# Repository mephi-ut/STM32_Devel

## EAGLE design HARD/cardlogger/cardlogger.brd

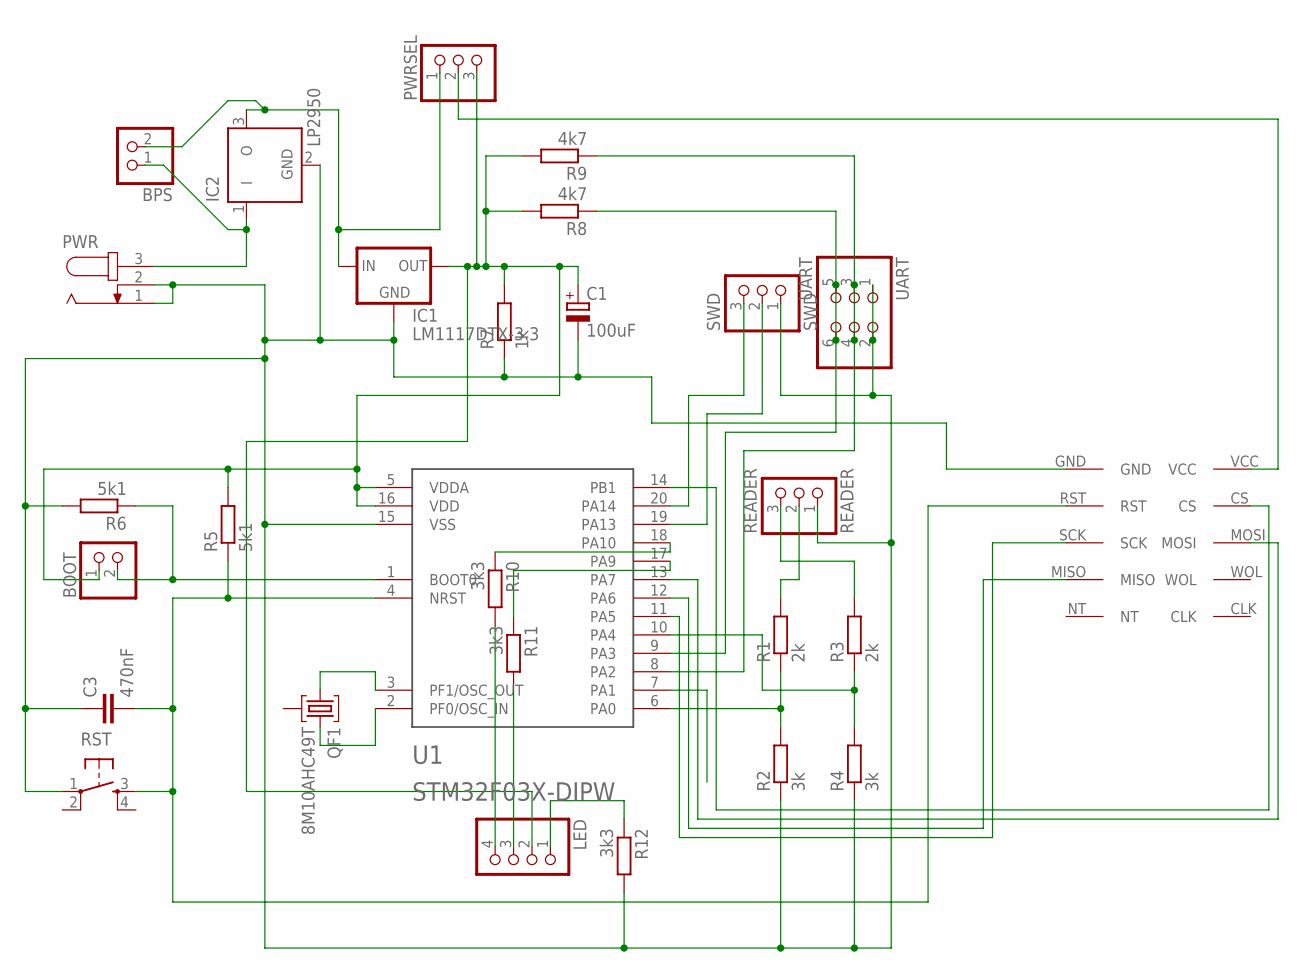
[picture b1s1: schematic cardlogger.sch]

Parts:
BOOT: PINHD-1X2; 1X02
BPS: PINHD-1X2; 1X02
C1: 100uF; SMC_D
C3: 470nF; C0805
IC1: LM1117DTX-3.3; TO252
IC2: LP2950; DPACK
LED: PINHD-1X4; 1X04
PWR: JACK-PLUG0; SPC4077
PWRSEL: PINHD-1X3; 1X03
QF1: 8M10AHC49T; HC49U
R1, R3: 2k; R1206
R2, R4: 3k; R1206
R5, R6: 5k1; R1206
R7: 1k; R1206
R8, R9: 4k7; R1206
R10, R11, R12: 3k3; R1206
READER: READER; 1X03
RST: TAC_SWITCHPTH; TACTILE-PTH
SWD: SWD; 1X03
U1: STM32F03X-DIPW; DIP20W
U$1: ENC28J60
UART: UART; 2X03

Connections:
+3V3: BOOT.1, C1.+, IC1.TAB (OUT), LED.2, PWRSEL.3, R5.2, R7.2, R8.2, R9.2, U1.5 (VDDA), U1.16 (VDD)
BOOT: BOOT.2, R6.1, U1.1 (BOOT0)
CR_0: R1.2, READER.2
CR_1: R3.2, READER.3
EXTI_1: R3.1, R4.2, U1.10 (PA4)
EXYI_0: R1.1, R2.2, U1.6 (PA0)
GND: C1.-, C3.1, IC1.1 (GND), IC2.2 (GND), PWR.1, PWR.2, R2.1, R4.1, R6.2, R7.1, R12.2, READER.1, RST.1, SWD.1, U1.15 (VSS), U$1.GND, UART.1, UART.2
unnamed: SWD.2, U1.19 (PA13)
unnamed: SWD.3, U1.20 (PA14)
unnamed: LED.4, R10.2
unnamed: U1.11 (PA5), U$1.SCK
unnamed: U1.12 (PA6), U$1.MISO
unnamed: U1.13 (PA7), U$1.MOSI
unnamed: U1.14 (PB1), U$1.CS
unnamed: R11.1, U1.17 (PA9)
unnamed: PWRSEL.2, U$1.VCC
unnamed: BPS.1, IC2.1 (I), PWR.3
unnamed: BPS.2, IC1.2 (IN), IC2.3 (O), PWRSEL.1
unnamed: R10.1, U1.18 (PA10)
unnamed: QF1.1, U1.3 (PF1/OSC_OUT)
unnamed: QF1.3, U1.2 (PF0/OSC_IN)
unnamed: LED.3, R11.2
unnamed: LED.1, R12.1
RST: C3.2, R5.1, RST.3, U1.4 (NRST), U$1.RST
RX: R8.1, U1.9 (PA3), UART.5, UART.6
TX: R9.1, U1.8 (PA2), UART.3, UART.4

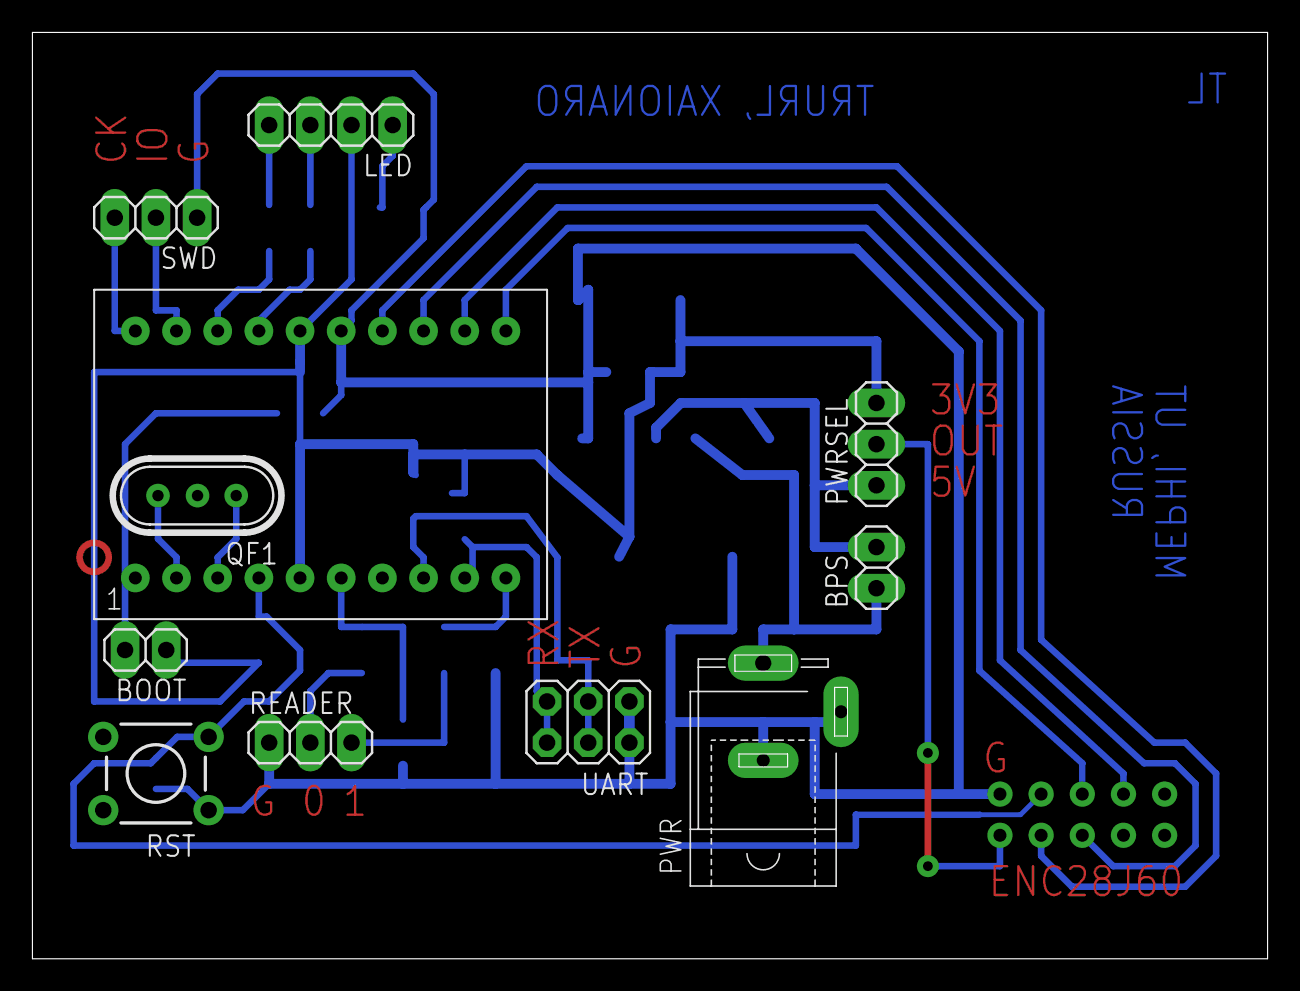
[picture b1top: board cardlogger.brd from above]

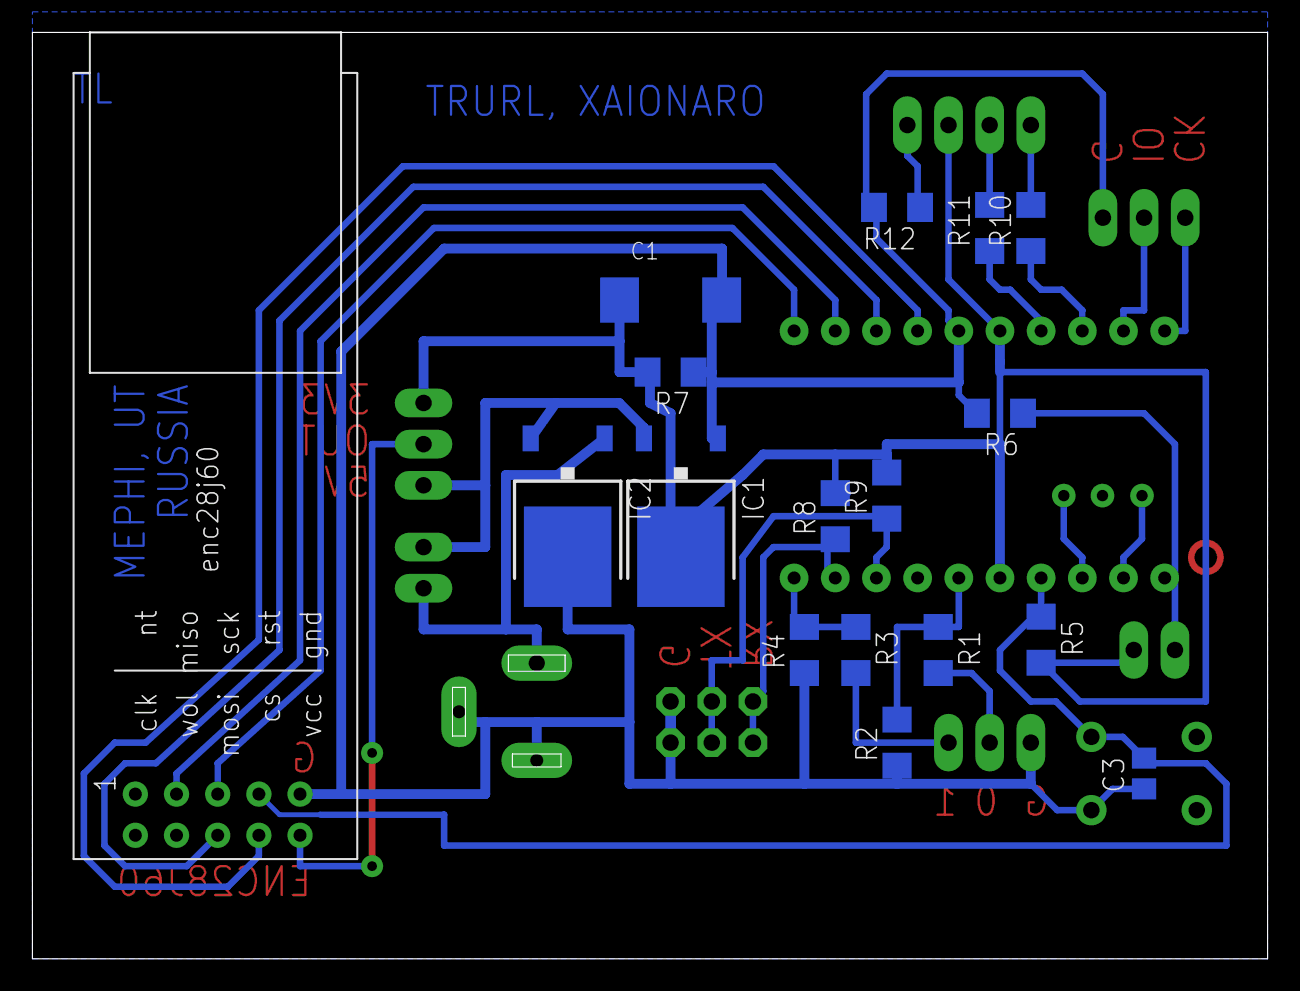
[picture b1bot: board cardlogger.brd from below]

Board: 2 copper layers, 76.2 x 57.1 mm, 28 parts (17 on the bottom side), 26 nets.

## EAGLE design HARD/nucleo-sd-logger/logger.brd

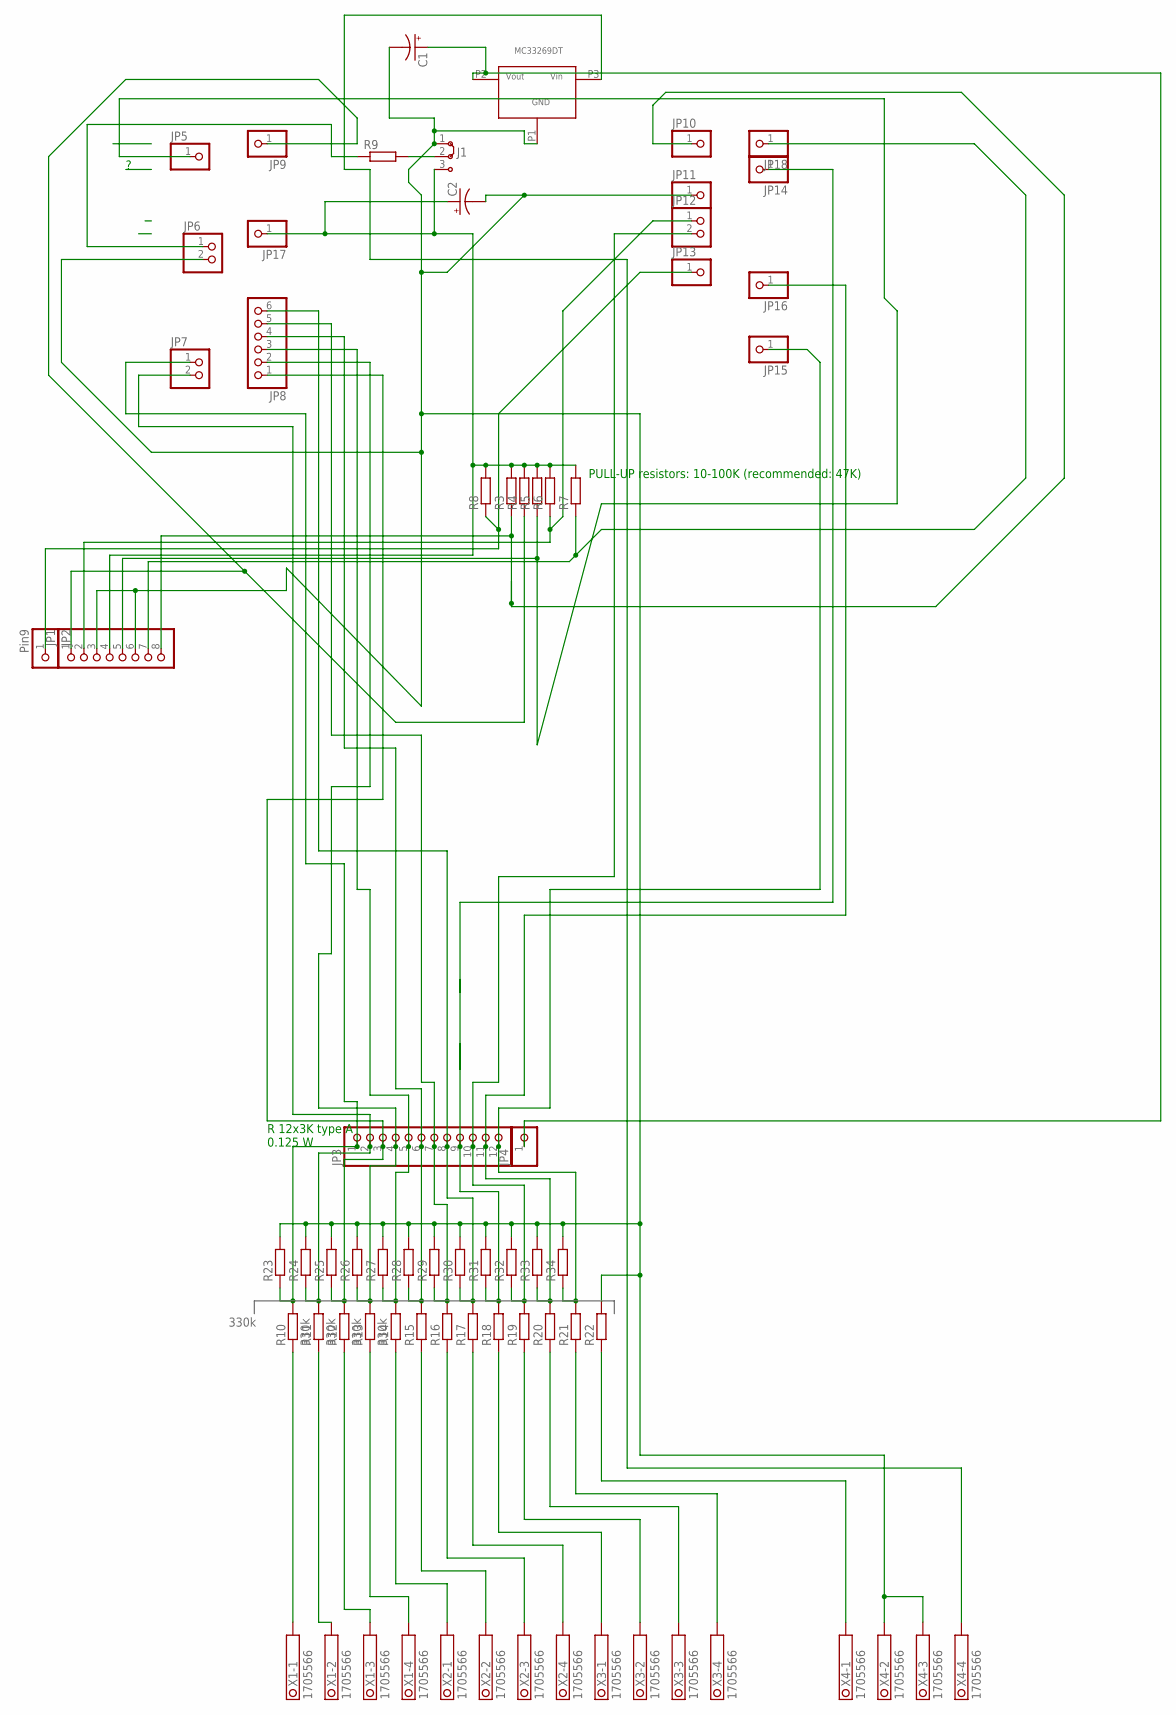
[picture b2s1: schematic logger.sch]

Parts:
C1, C2: CPOL-USE5-10.5; E5-10,5
J1: J2X2MM; 04C
JP1: PINHD-1X8; 1X08
JP2: Pin9; 1X01
JP3: PINHD-1X12; 1X12
JP4, JP5, JP9, JP10, JP11, JP13, JP14, JP15, JP16, JP17, JP18: PINHD-1X1; 1X01
JP6, JP7, JP12: PINHD-1X2; 1X02
JP8: PINHD-1X6; 1X06
R3, R4, R5, R6, R7, R8, R9, R23, R24, R25, R26, R27, R28, R29, R30, R31, R32, R33, R34: R-EU_R1206; R1206
R10, R11, R12, R13: 330k; 0207/15
R14, R15, R16, R17, R18, R19, R20, R21, R22: R-EU_0207/15; 0207/15
U$2: MC33269DT
X1, X2, X3, X4: 1705566

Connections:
unnamed: JP1.7, JP18.1, R7.1
unnamed: U$2.P3 (VIN), X4.4.1, X4.4.2
unnamed: JP6.1, R9.1
unnamed: C1.-, C2.-, J1.1, JP1.3, JP1.6, JP6.2, JP11.1, R22.2, R23.2, R24.2, R25.2, R26.2, R27.2, R28.2, R29.2, R30.2, R31.2, R32.2, R33.2, R34.2, U$2.P1 (GND), X4.2.1, X4.2.2, X4.3.1, X4.3.2
unnamed: JP2.1, JP13.1, R8.1
unnamed: JP1.1, JP9.1, R4.1
unnamed: JP1.2, JP12.1, R6.1
unnamed: JP1.5, JP5.1, R5.1
unnamed: JP1.8, JP10.1, R3.1
unnamed: JP3.8, JP8.6, R17.2, R30.1
unnamed: JP3.7, JP8.5, R16.2, R29.1
unnamed: JP3.6, JP8.4, R15.2, R28.1
unnamed: JP3.5, JP8.3, R14.2, R27.1
unnamed: JP3.2, JP7.2, R11.2, R24.1
unnamed: R22.1, X4.1.1, X4.1.2
unnamed: C2.+, J1.3, JP1.4, JP17.1, R3.2, R4.2, R5.2, R6.2, R7.2, R8.2
unnamed: JP3.10, JP12.2, R19.2, R32.1
unnamed: JP3.3, JP8.1, R12.2, R25.1
unnamed: JP3.11, JP16.1, R20.2, R33.1
unnamed: JP3.1, JP7.1, R10.2, R23.1
unnamed: C1.+, JP4.1, U$2.P2 (VOUT)
unnamed: J1.2, R9.2
unnamed: JP3.4, JP8.2, R13.2, R26.1
unnamed: JP3.12, JP15.1, R21.2, R34.1
unnamed: JP3.9, JP14.1, R18.2, R31.1
unnamed: R10.1, X1.1.1, X1.1.2
unnamed: R11.1, X1.2.1, X1.2.2
unnamed: R12.1, X1.3.1, X1.3.2
unnamed: R13.1, X1.4.1, X1.4.2
unnamed: R14.1, X2.1.1, X2.1.2
unnamed: R15.1, X2.2.1, X2.2.2
unnamed: R16.1, X2.3.1, X2.3.2
unnamed: R17.1, X2.4.1, X2.4.2
unnamed: R18.1, X3.1.1, X3.1.2
unnamed: R19.1, X3.2.1, X3.2.2
unnamed: R20.1, X3.3.1, X3.3.2
unnamed: R21.1, X3.4.1, X3.4.2

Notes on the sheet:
PULL-UP resistors: 10-100K (recommended: 47K)
330k
R 12x3K type A 0.125 W

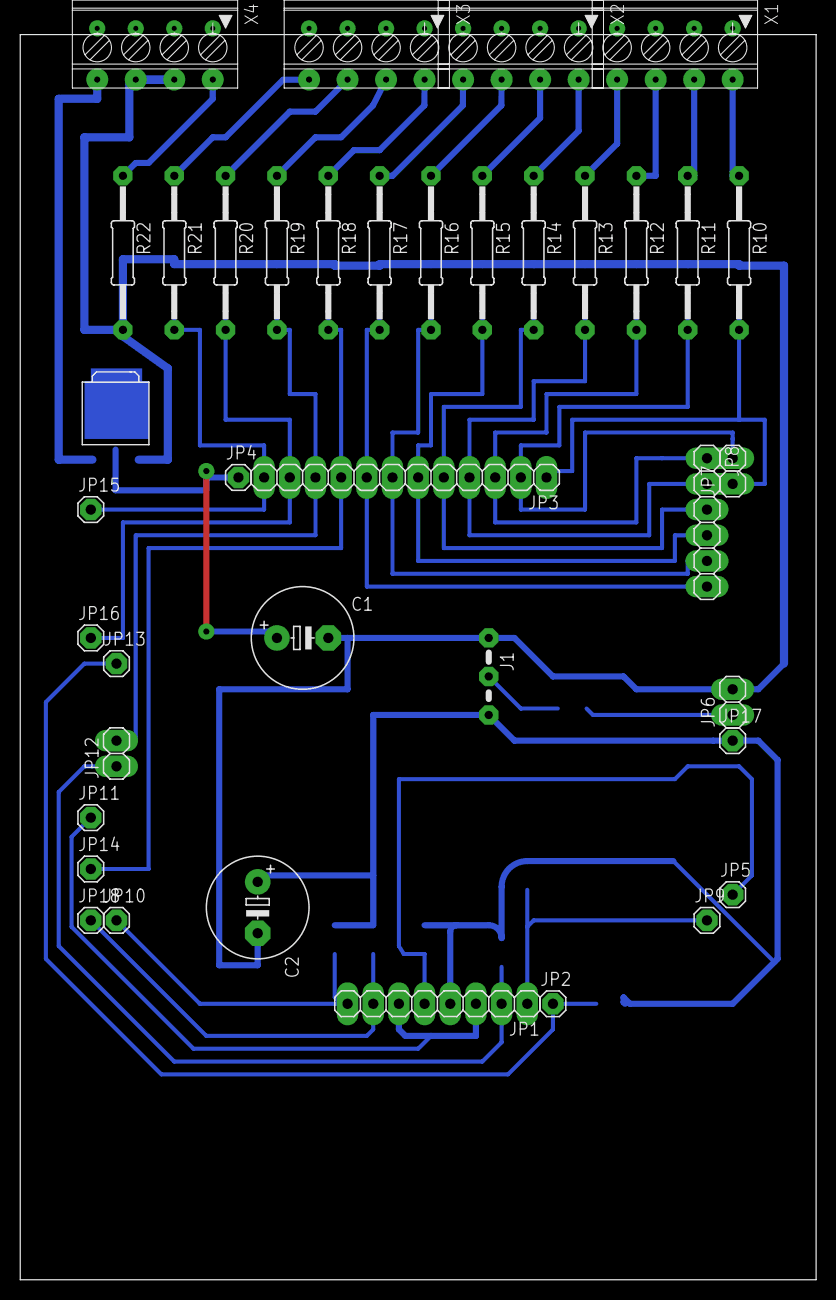
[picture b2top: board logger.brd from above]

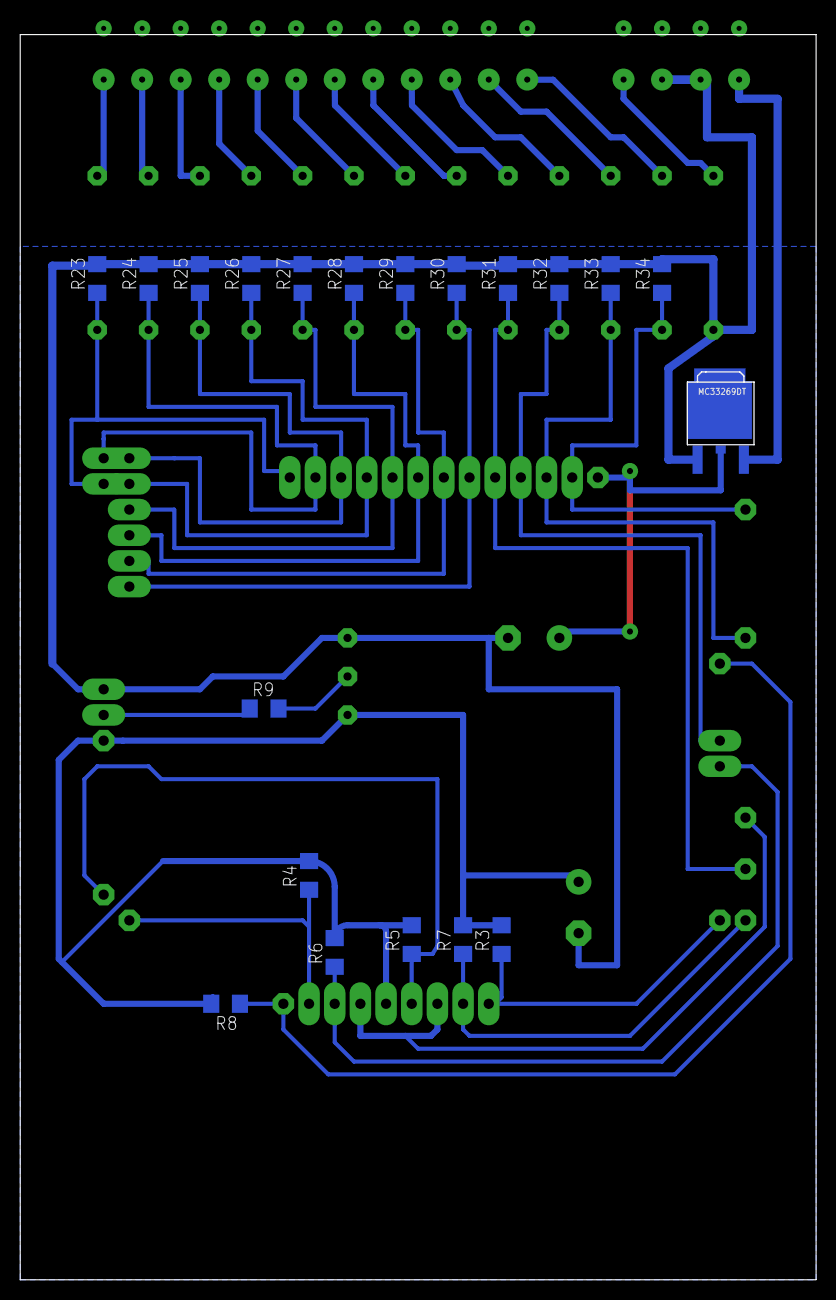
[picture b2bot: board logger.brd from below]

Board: 2 copper layers, 78.7 x 123.2 mm, 58 parts (20 on the bottom side), 37 nets.

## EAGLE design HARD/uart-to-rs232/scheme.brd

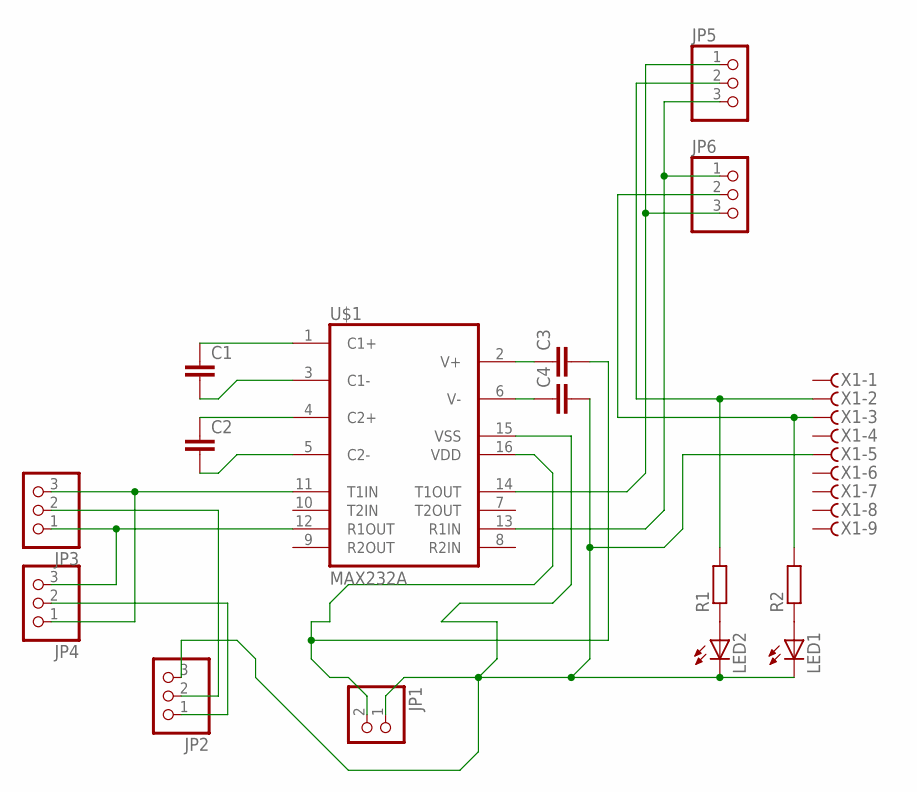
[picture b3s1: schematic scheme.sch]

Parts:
C1, C2, C3, C4: C-EUC1206; C1206
JP1: PINHD-1X2; 1X02
JP2, JP3, JP4, JP5, JP6: PINHD-1X3; 1X03
LED1, LED2: LED3MM
R1, R2: R-EU_R1206; R1206
U$1: MAX232A; SO16
X1: F09HS; F09H

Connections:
unnamed: C1.1, U$1.1 (C1+)
unnamed: C1.2, U$1.3 (C1-)
unnamed: C2.1, U$1.4 (C2+)
unnamed: C2.2, U$1.5 (C2-)
unnamed: C3.2, JP1.2, U$1.16 (VDD)
unnamed: JP3.3, JP4.1, U$1.11 (T1IN)
unnamed: JP3.1, JP4.3, U$1.12 (R1OUT)
unnamed: JP2.2, JP3.2
unnamed: JP2.1, JP4.2
unnamed: JP6.2, R2.2, X1.3
unnamed: C3.1, U$1.2 (V+)
unnamed: C4.1, U$1.6 (V-)
unnamed: JP5.1, JP6.3, U$1.14 (T1OUT)
unnamed: C4.2, JP1.1, JP2.3, LED1.K (C), LED2.K (C), U$1.15 (VSS), X1.5
unnamed: JP5.2, R1.2, X1.2
unnamed: JP5.3, JP6.1, U$1.13 (R1IN)
unnamed: LED1.A, R2.1
unnamed: LED2.A, R1.1

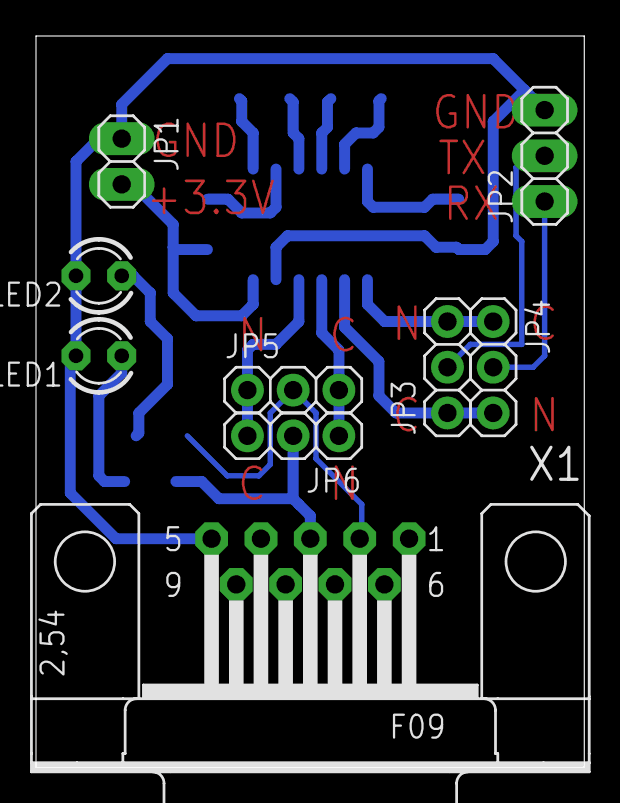
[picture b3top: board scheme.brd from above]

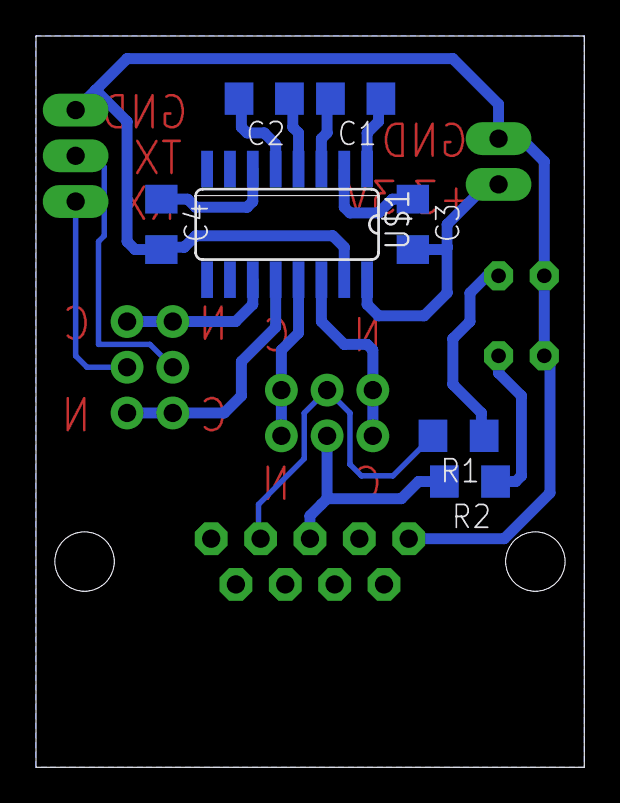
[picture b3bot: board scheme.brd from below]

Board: 2 copper layers, 30.5 x 40.6 mm, 16 parts (7 on the bottom side), 18 nets.

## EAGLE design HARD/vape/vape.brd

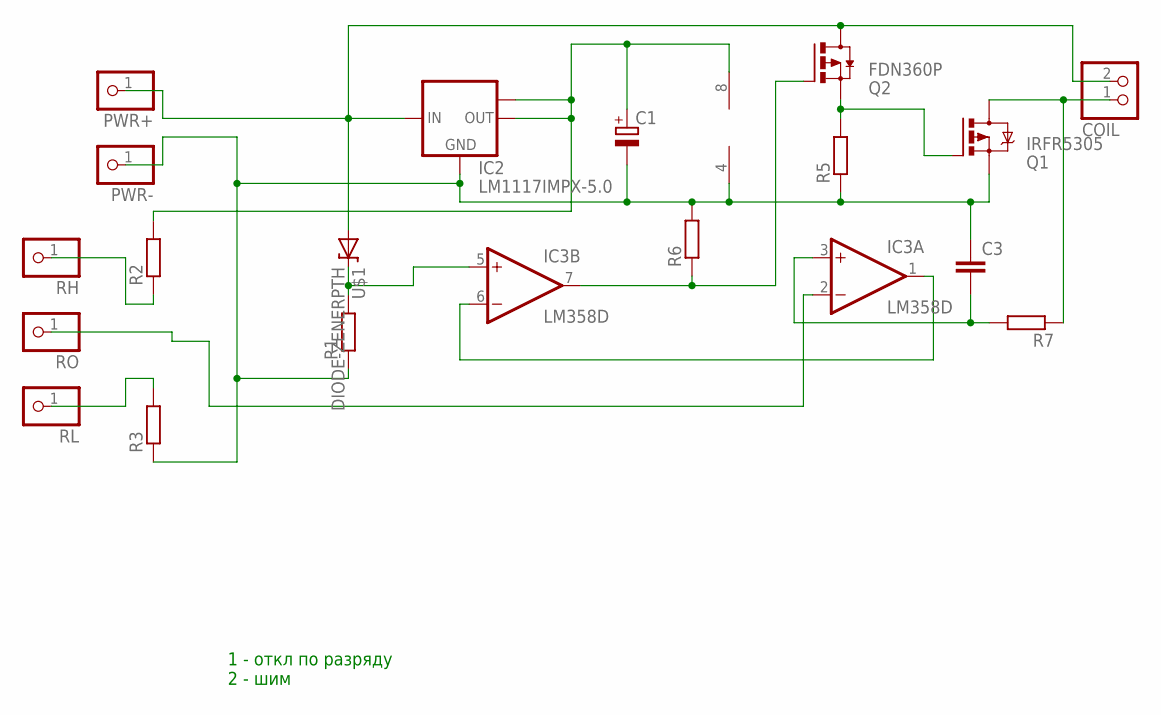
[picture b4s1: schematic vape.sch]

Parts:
C1: CPOL-EUSMCD; SMC_D
C3: C-EUC1206; C1206
COIL: PINHD-1X2; 1X02
IC2: LM1117IMPX-5.0; SOT223
IC3: LM358D; SO08
PWR+: PINHD-1X1; 1X01
PWR-: PINHD-1X1; 1X01
Q1: IRFR5305; D-PAK_TO252AA
Q2: FDN360P; SUPER-SOT3
R1, R2, R3, R5, R6, R7: R-EU_R1206; R1206
RH: PINHD-1X1; 1X01
RL: PINHD-1X1; 1X01
RO: PINHD-1X1; 1X01
U$1: DIODE-ZENERPTH; DIODE-ZENER

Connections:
unnamed: COIL.2, IC2.3 (IN), PWR+.1, Q2.3 (D), U$1.P$2 (A)
unnamed: IC3.1 (OUT), IC3.6 (-IN)
unnamed: C1.-, C3.1, IC2.1 (GND), IC3.4 (V-), PWR-.1, Q1.3 (S), R1.1, R3.1, R5.1, R6.2
unnamed: C3.2, IC3.3 (+IN), R7.2
unnamed: IC3.7 (OUT), Q2.1 (G), R6.1
unnamed: C1.+, IC2.2 (OUT), IC2.TAB (OUT1), IC3.8 (V+), R2.2
unnamed: R2.1, RH.1
unnamed: Q1.1 (G), Q2.2 (S), R5.2
unnamed: R3.2, RL.1
unnamed: IC3.5 (+IN), R1.2, U$1.P$1 (C)
unnamed: COIL.1, Q1.4 (D), R7.1
unnamed: IC3.2 (-IN), RO.1

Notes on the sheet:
1 - откл по разряду 2 - шим

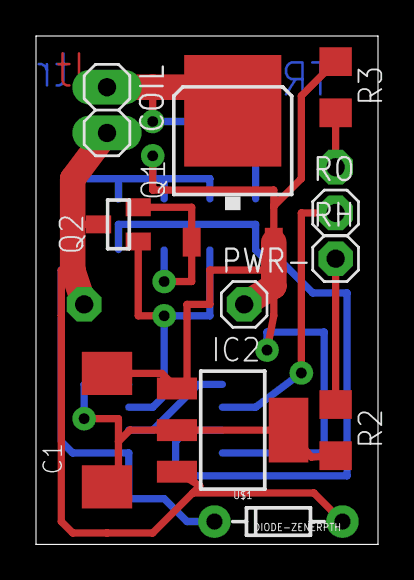
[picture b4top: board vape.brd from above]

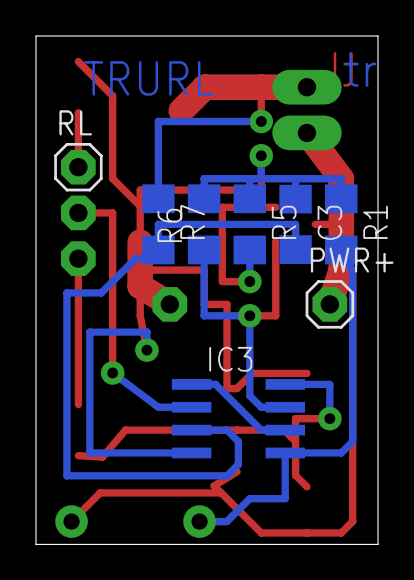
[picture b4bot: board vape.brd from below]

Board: 2 copper layers, 19.0 x 28.2 mm, 19 parts (8 on the bottom side), 12 nets.

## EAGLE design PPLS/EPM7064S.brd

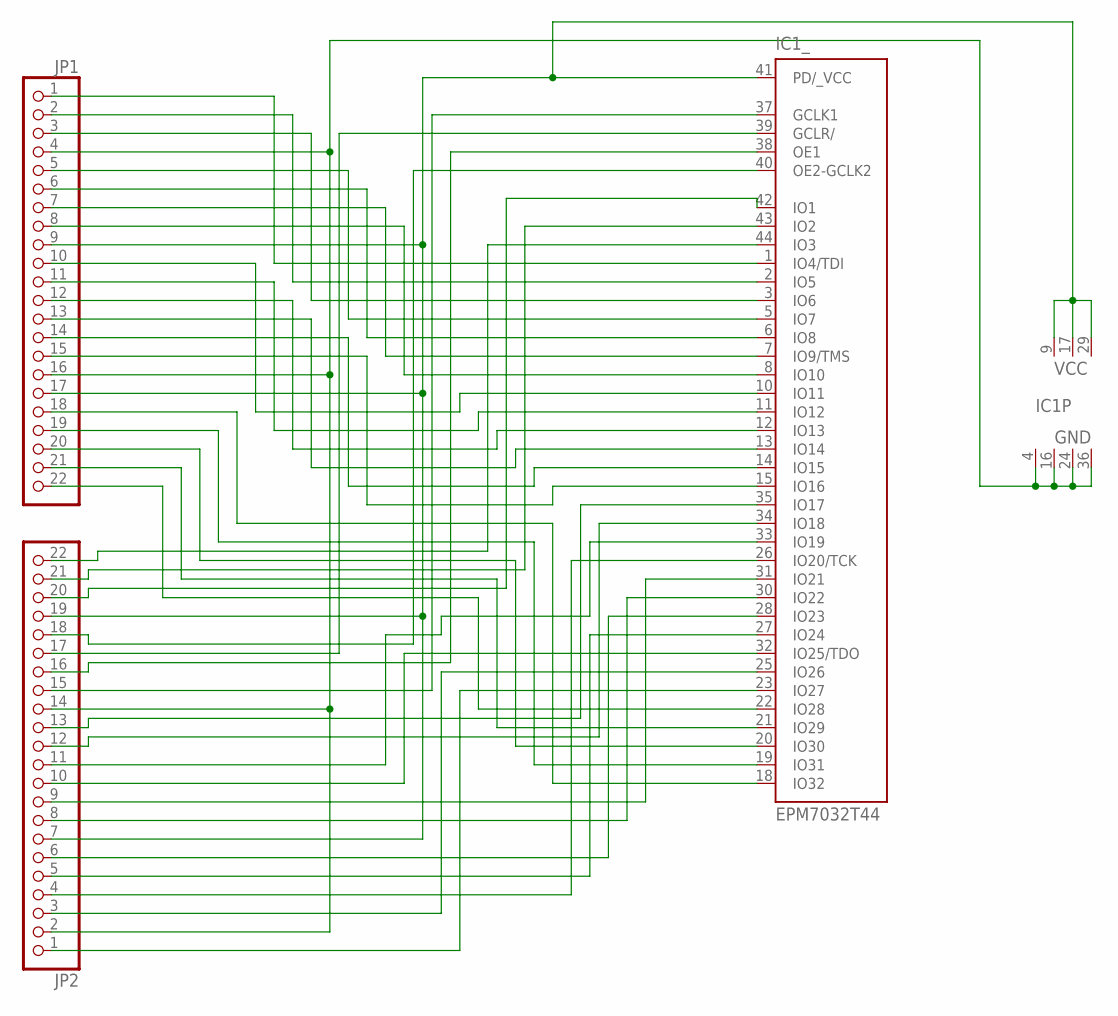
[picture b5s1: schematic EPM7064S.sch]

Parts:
IC1: EPM7032T44; TQFP44
JP1, JP2: PINHD-1X22; 1X22

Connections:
unnamed: IC1.1 (IO4/TDI), JP1.1
unnamed: IC1.2 (IO5), JP1.2
unnamed: IC1.3 (IO6), JP1.3
unnamed: IC1.4 (GND), IC1.16 (GND), IC1.24 (GND), IC1.36 (GND), JP1.4, JP1.16, JP2.2, JP2.14
unnamed: IC1.9 (VCC), IC1.17 (VCC), IC1.29 (VCC), IC1.41 (PD/_VCC), JP1.9, JP1.17, JP2.7, JP2.19
unnamed: IC1.5 (IO7), JP1.5
unnamed: IC1.6 (IO8), JP1.6
unnamed: IC1.7 (IO9/TMS), JP1.7
unnamed: IC1.8 (IO10), JP1.8
unnamed: IC1.10 (IO11), JP1.10
unnamed: IC1.11 (IO12), JP1.11
unnamed: IC1.12 (IO13), JP1.12
unnamed: IC1.13 (IO14), JP1.13
unnamed: IC1.14 (IO15), JP1.14
unnamed: IC1.15 (IO16), JP1.15
unnamed: IC1.18 (IO32), JP1.18
unnamed: IC1.19 (IO31), JP1.19
unnamed: IC1.20 (IO30), JP1.20
unnamed: IC1.21 (IO29), JP1.21
unnamed: IC1.22 (IO28), JP1.22
unnamed: IC1.23 (IO27), JP2.1
unnamed: IC1.25 (IO26), JP2.3
unnamed: IC1.26 (IO20/TCK), JP2.4
unnamed: IC1.27 (IO24), JP2.5
unnamed: IC1.28 (IO23), JP2.6
unnamed: IC1.30 (IO22), JP2.8
unnamed: IC1.31 (IO21), JP2.9
unnamed: IC1.32 (IO25/TDO), JP2.10
unnamed: IC1.33 (IO19), JP2.11
unnamed: IC1.34 (IO18), JP2.12
unnamed: IC1.35 (IO17), JP2.13
unnamed: IC1.37 (GCLK1), JP2.15
unnamed: IC1.38 (OE1), JP2.16
unnamed: IC1.39 (GCLR/), JP2.17
unnamed: IC1.40 (OE2-GCLK2), JP2.18
unnamed: IC1.42 (IO1), JP2.20
unnamed: IC1.43 (IO2), JP2.21
unnamed: IC1.44 (IO3), JP2.22

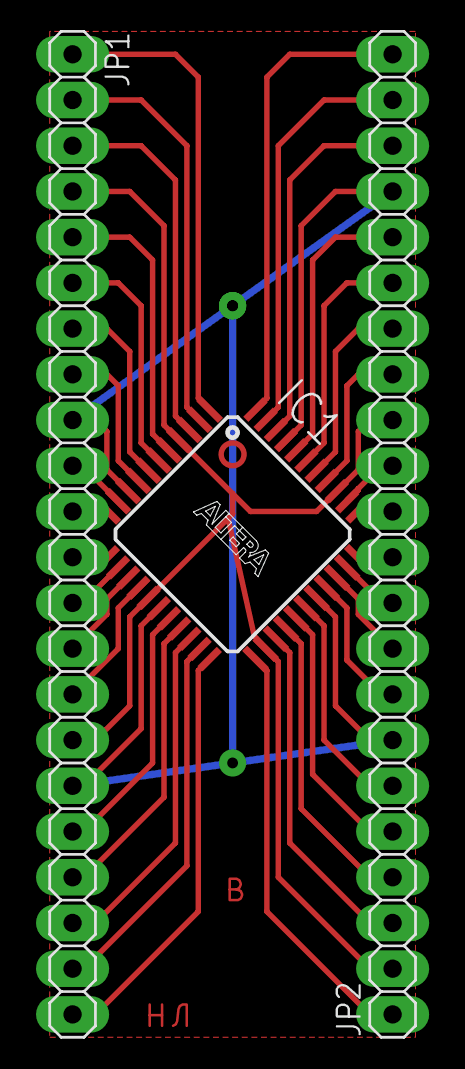
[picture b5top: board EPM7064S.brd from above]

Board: 2 copper layers, 3 parts (0 on the bottom side), 38 nets.

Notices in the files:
parts and their libraries:
SparkFun: Licensing: CC v3.0 Share-Alike You are welcome to use this library for commercial purposes.
